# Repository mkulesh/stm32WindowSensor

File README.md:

# stm32WindowSensor

*RF window sensors: STM32L + RFM69 + Android*

This is a DIY windows monitorig system that consist of:
- A window sensor based on STM32L051 MCU and RFM69 RF module. The PCB is developed in EagleCad, firmware written in C++ using System Workbench for STM32
- A server unit also based on STM32L051 MCU and RFM69 RF module
- A server software module (Java) that reads data from server unit and forwards it to the mobile app
- A mobile app for Android written in Java

## Window Sensor

## Server Unit

## Android App

## License

This software is published under the *GNU General Public License, Version 3*

Copyright © 2018-2019 by Mikhail Kulesh

This program is free software: you can redistribute it and/or modify it under the terms of the GNU General Public License as
published by the Free Software Foundation, either version 3 of the License, or (at your option) any later version.

This program is distributed in the hope that it will be useful, but WITHOUT ANY WARRANTY; without even the implied warranty
of MERCHANTABILITY or FITNESS FOR A PARTICULAR PURPOSE.  See the GNU General Public License for more details. You should have
received a copy of the GNU General Public License along with this program.

If not, see [www.gnu.org/licenses](https://www.gnu.org/licenses).

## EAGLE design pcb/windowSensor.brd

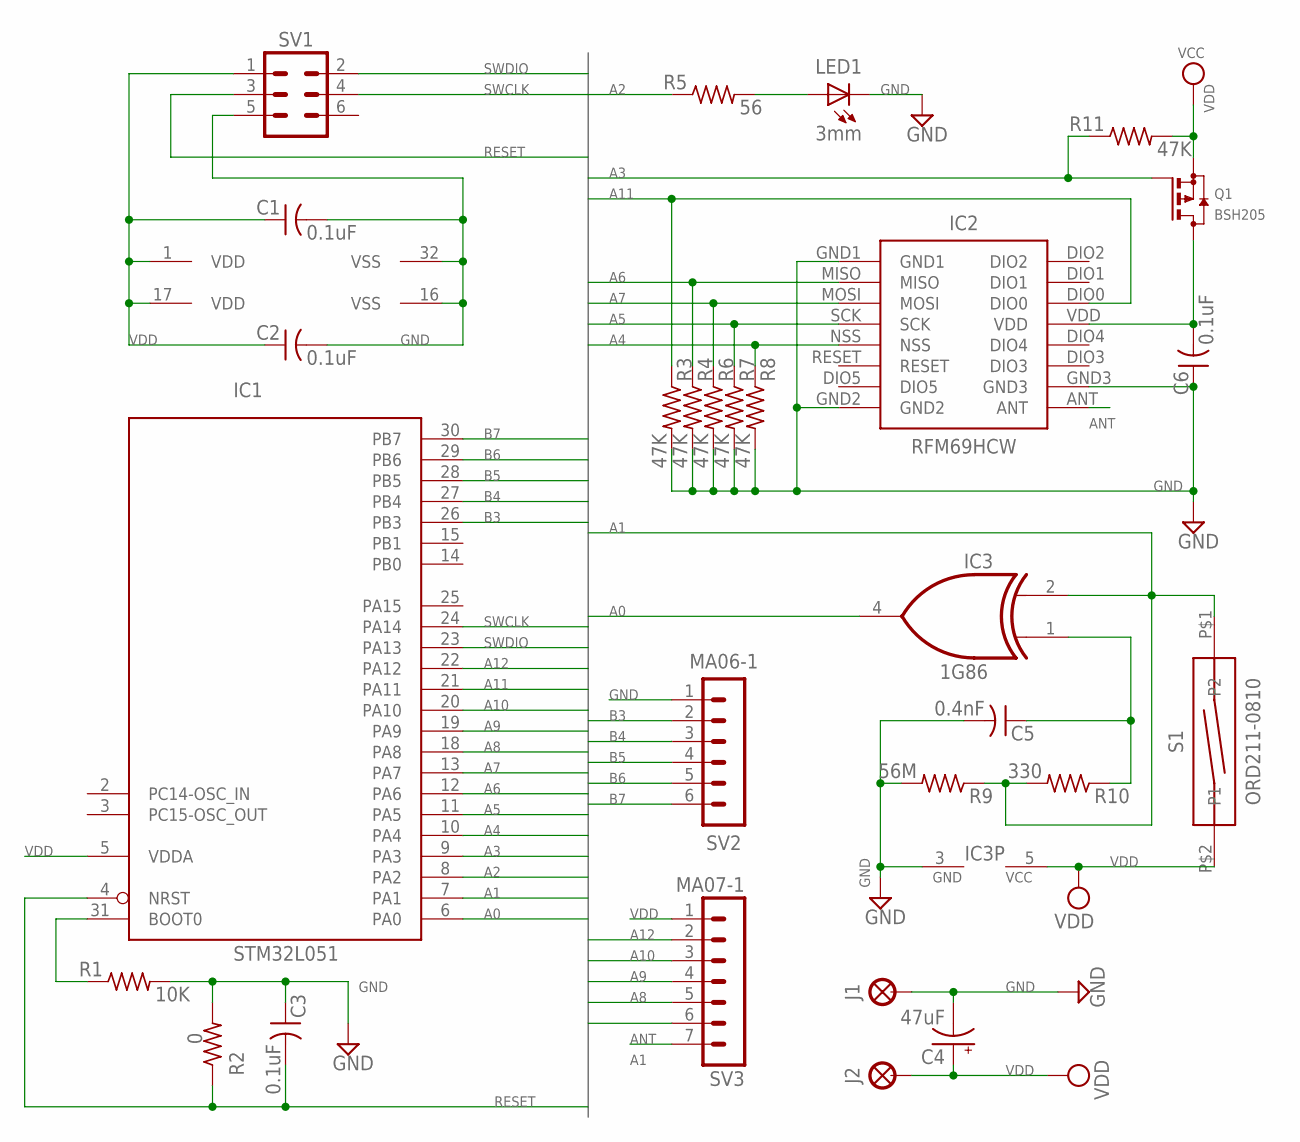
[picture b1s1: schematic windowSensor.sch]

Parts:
C1, C2, C3, C6: 0.1uF; C0805
C4: 47uF; CPOL0805
C5: 0.4nF; C0805
IC1: STM32L051; LQFP32
IC2: RFM69HCW
IC3: 1G86; SC70-5
J1, J2: LSP30-LONG
LED1: 3mm; LED3MM
Q1: BSH205; SOT23
R1: 10K; R0805
R2: 0; R0805
R3, R4, R6, R7, R8, R11: 47K; R0805
R5: 56; R0805
R9: 56M; R0805
R10: 330; R0805
S1: ORD211-0810
SV1: SWD; MA03-2
SV2: MA06-1; MA06-1-NO-PL
SV3: MA07-1; MA07-1-NO-PL

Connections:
A0: IC1.6 (PA0), IC3.4 (O)
A1: IC1.7 (PA1), IC3.2 (I1), R9.1, R10.2, S1.P$1 (P2), SV3.6
A2: IC1.8 (PA2), R5.1
A3: IC1.9 (PA3), Q1.1 (G), R11.1
A4: IC1.10 (PA4), IC2.NSS, R8.1
A5: IC1.11 (PA5), IC2.SCK, R7.1
A6: IC1.12 (PA6), IC2.MISO, R4.1
A7: IC1.13 (PA7), IC2.MOSI, R6.1
A8: IC1.18 (PA8), SV3.5
A9: IC1.19 (PA9), SV3.4
A10: IC1.20 (PA10), SV3.3
A11: IC1.21 (PA11), IC2.DIO0, R3.1
A12: IC1.22 (PA12), SV3.2
A-BOOT: IC1.31 (BOOT0), R1.1
ANT: IC2.ANT, SV3.7
B3: IC1.26 (PB3), SV2.2
B4: IC1.27 (PB4), SV2.3
B5: IC1.28 (PB5), SV2.4
B6: IC1.29 (PB6), SV2.5
B7: IC1.30 (PB7), SV2.6
GND: C1.2, C2.2, C3.1, C4.2- (-), C5.2, C6.1, IC1.16 (VSS), IC1.32 (VSS), IC2.GND1, IC2.GND2, IC2.GND3, IC3.3 (GND), J1.MP, LED1.K (C), R1.2, R2.2, R3.2, R4.2, R6.2, R7.2, R8.2, R9.2, SV1.5, SV2.1
unnamed: LED1.A, R5.2
unnamed: C5.1, IC3.1 (I0), R10.1
RESET: C3.2, IC1.4 (NRST), R2.1, SV1.3
SD-VDD: C6.2, IC2.VDD, Q1.3 (D)
SWCLK: IC1.24 (PA14), SV1.4
SWDIO: IC1.23 (PA13), SV1.2
VDD: C1.1, C2.1, C4.1+ (+), IC1.1 (VDD), IC1.5 (VDDA), IC1.17 (VDD), IC3.5 (VCC), J2.MP, Q1.2 (S), R11.2, S1.P$2 (P1), SV1.1, SV3.1

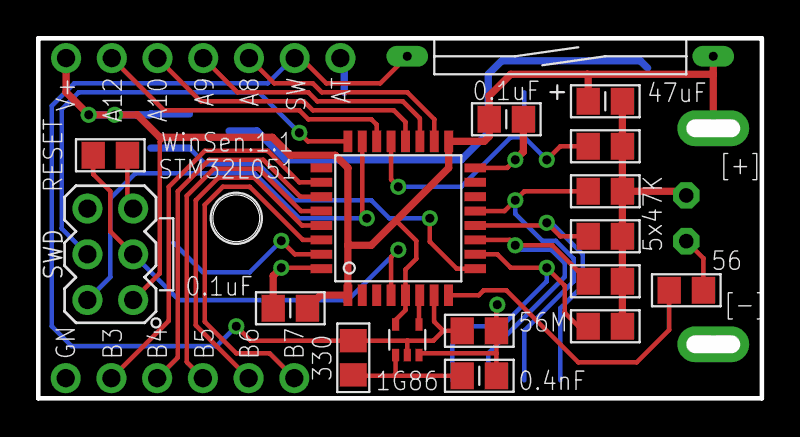
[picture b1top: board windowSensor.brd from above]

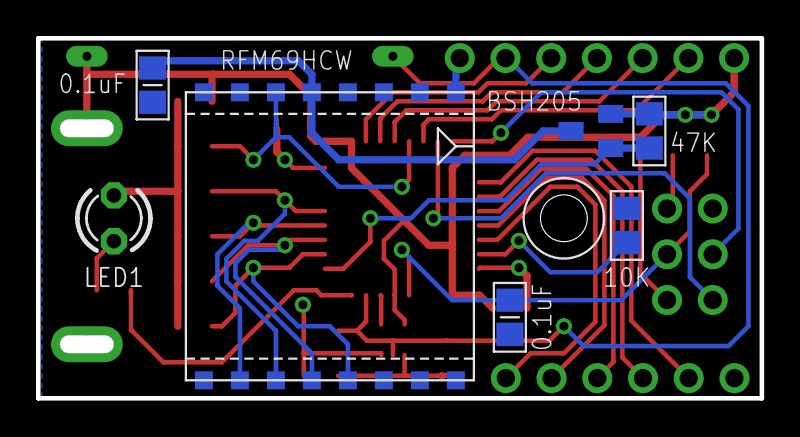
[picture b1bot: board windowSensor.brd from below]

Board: 2 copper layers, 40.2 x 20.0 mm, 28 parts (7 on the bottom side), 28 nets.

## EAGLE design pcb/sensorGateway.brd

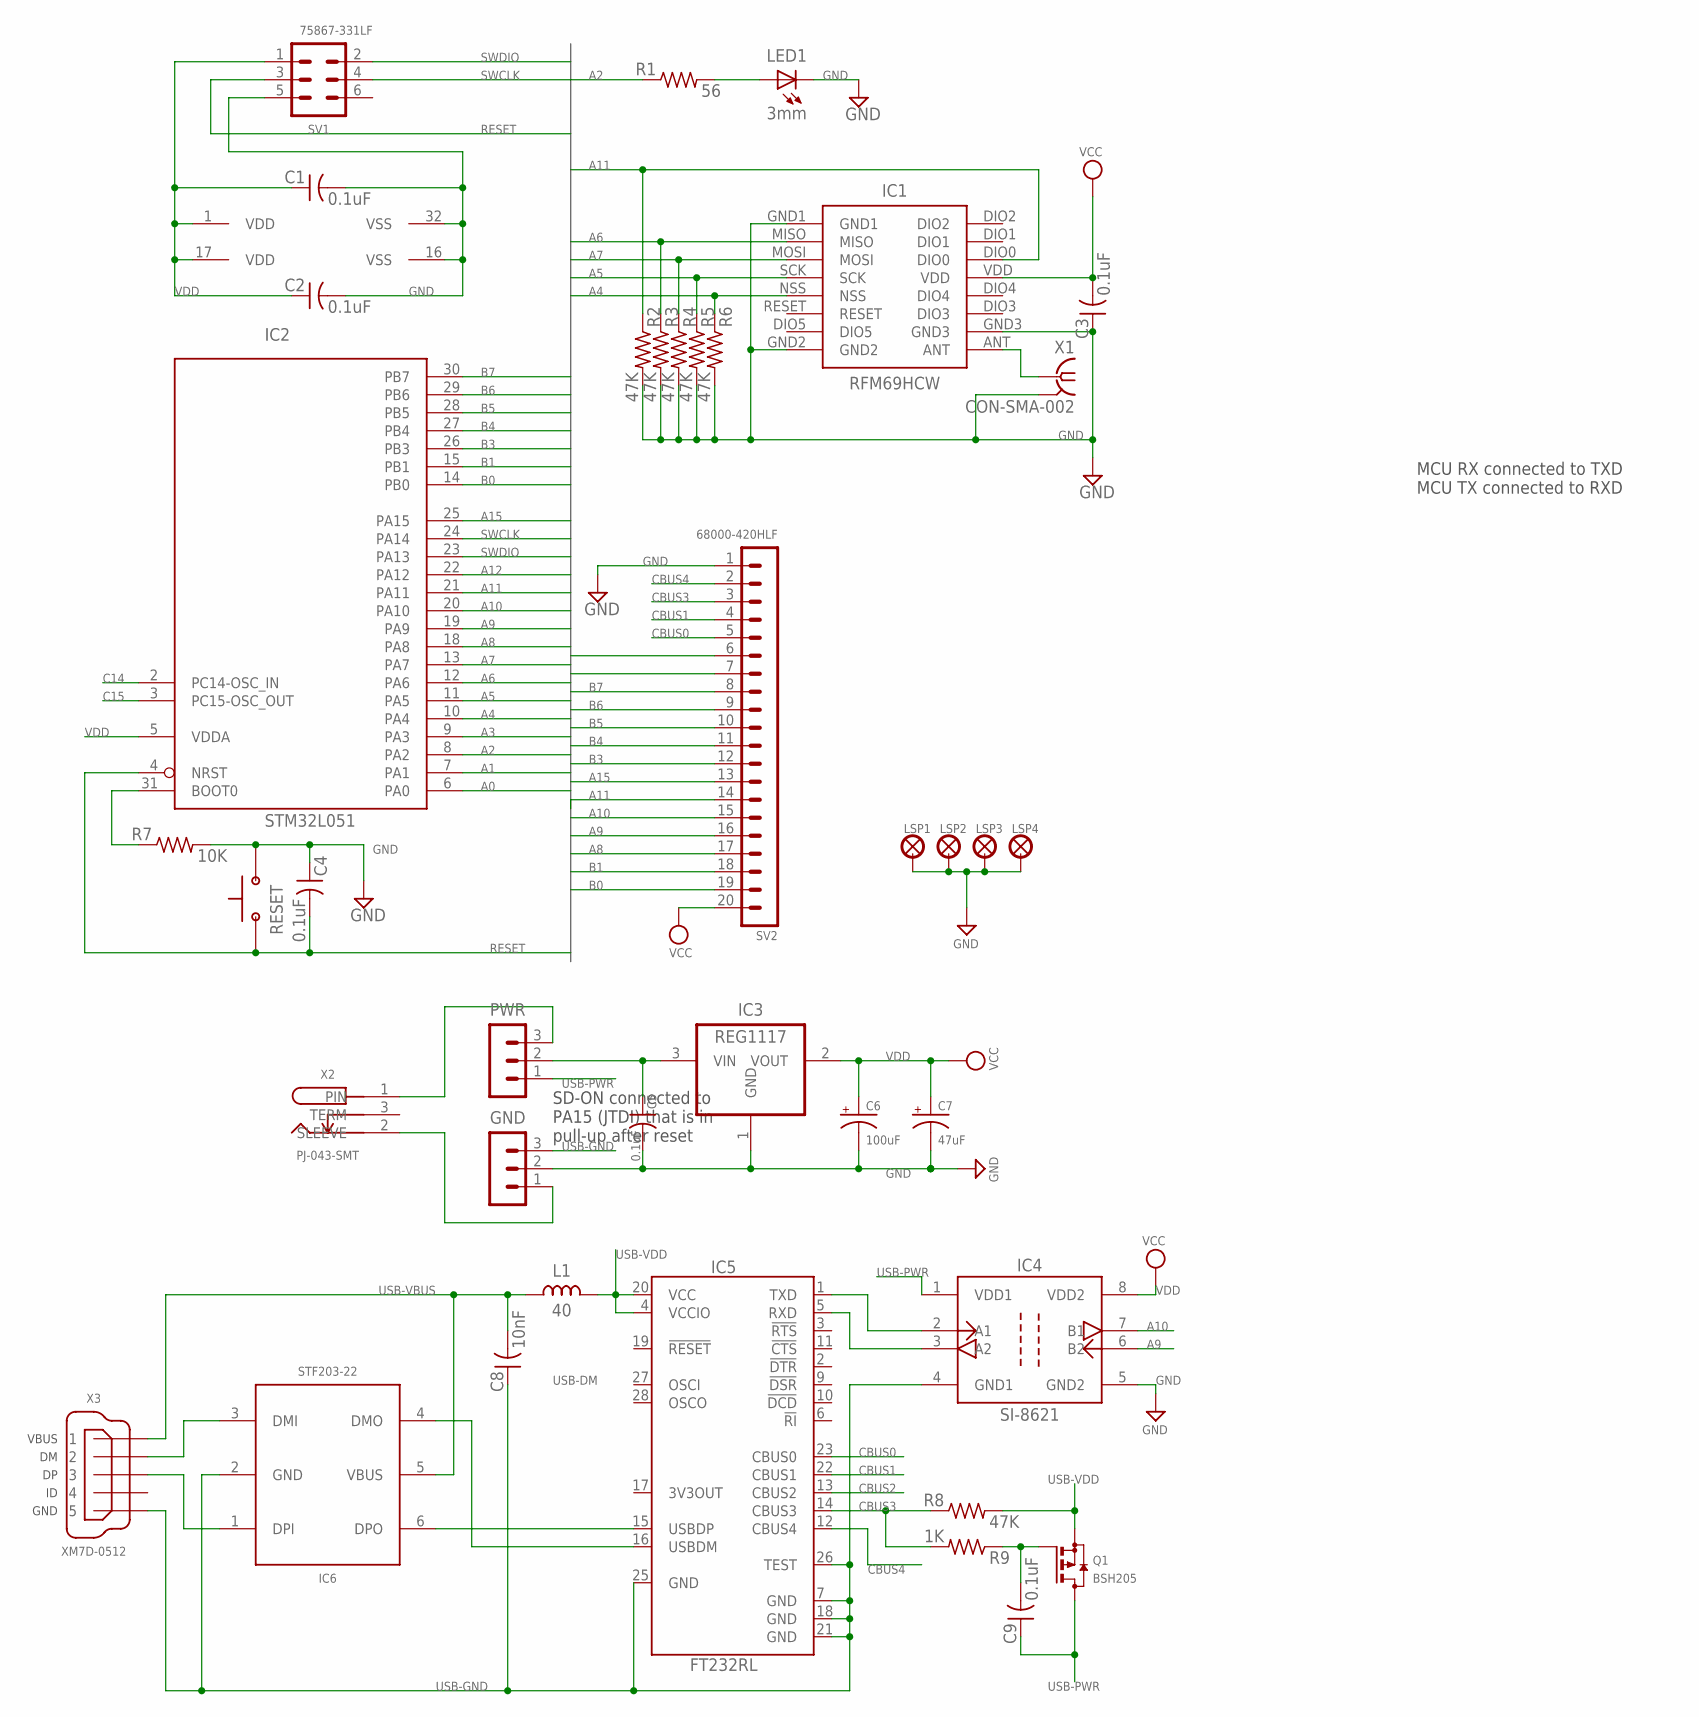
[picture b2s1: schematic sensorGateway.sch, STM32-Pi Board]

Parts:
C1, C2, C3, C4, C5, C9: 0.1uF; C0805
C6: 100uF; CPOL1311
C7: 47uF; CPOL0805
C8: 10nF; C0805
GND: MA03-1PL; MA03-1
IC1: RFM69HCW
IC2: STM32L051; LQFP32
IC3: REG1117; SOT223
IC4: SI-8621; SOIC-8
IC5: FT232RL; SSOP28
IC6: STF203-22; SC70-6
L1: 40; L0805
LED1: 3mm; LED3MM
LSP1, LSP2, LSP3, LSP4: LSP27
PWR: MA03-1PL; MA03-1
Q1: BSH205; SOT23
R1: 56; R0805
R2, R3, R4, R5, R6, R8: 47K; R0805
R7: 10K; R0805
R9: 1K; R0805
RESET: BUTTON-FSM14JRT
SV1: 75867-331LF; MA03-2
SV2: 68000-420HLF; MA20-1-NO-PL
X1: CON-SMA-002; BU-SMA-G
X2: PJ-043-SMT; BUCHSE-1.0X3.2
X3: XM7D-0512

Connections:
A0: IC2.6 (PA0)
A1: IC2.7 (PA1)
A2: IC2.8 (PA2), R1.1
A3: IC2.9 (PA3)
A4: IC1.NSS, IC2.10 (PA4), R6.1
A5: IC1.SCK, IC2.11 (PA5), R5.1
A6: IC1.MISO, IC2.12 (PA6), R3.1
A7: IC1.MOSI, IC2.13 (PA7), R4.1
A8: IC2.18 (PA8), SV2.17
A9: IC2.19 (PA9), IC4.6 (B2), SV2.16
A10: IC2.20 (PA10), IC4.7 (B1), SV2.15
A11: IC1.DIO0, IC2.21 (PA11), R2.1, SV2.14
A12: IC2.22 (PA12)
A15: IC2.25 (PA15), SV2.13
A-BOOT: IC2.31 (BOOT0), R7.1
B0: IC2.14 (PB0), SV2.19
B1: IC2.15 (PB1), SV2.18
B3: IC2.26 (PB3), SV2.12
B4: IC2.27 (PB4), SV2.11
B5: IC2.28 (PB5), SV2.10
B6: IC2.29 (PB6), SV2.9
B7: IC2.30 (PB7), SV2.8
C14: IC2.2 (PC14-OSC_IN), SV2.7
C15: IC2.3 (PC15-OSC_OUT), SV2.6
CBUS0: IC5.23 (CBUS0), SV2.5
CBUS1: IC5.22 (CBUS1), SV2.4
CBUS2: IC5.13 (CBUS2)
CBUS3: IC5.14 (CBUS3), R8.1, R9.2, SV2.3
CBUS4: IC5.12 (CBUS4), SV2.2
GND: C1.2, C2.2, C3.1, C4.1, C5.2, C6.2- (-), C7.2- (-), GND.2, IC1.GND1, IC1.GND2, IC1.GND3, IC2.16 (VSS), IC2.32 (VSS), IC3.1 (GND), IC4.5 (GND2), LED1.K (C), LSP1.MP, LSP2.MP, LSP3.MP, LSP4.MP, R2.2, R3.2, R4.2, R5.2, R6.2, R7.2, RESET.P$2 (2), SV1.5, SV2.1, X1.2, X1.3 (2), X1.4 (2), X1.5 (2)
unnamed: LED1.A, R1.2
unnamed: IC1.ANT, X1.1
unnamed: C9.2, Q1.1 (G), R9.1
unnamed: IC4.2 (A1), IC5.1 (TXD)
unnamed: GND.1, X2.2 (SLEEVE)
unnamed: IC4.3 (A2), IC5.5 (RXD)
unnamed: PWR.3, X2.1 (PIN)
unnamed: IC6.1 (DPI), X3.3
unnamed: IC6.3 (DMI), X3.2
RESET: C4.2, IC2.4 (NRST), RESET.P$1 (1), SV1.3
SWCLK: IC2.24 (PA14), SV1.4
SWDIO: IC2.23 (PA13), SV1.2
USB-DM: IC5.16 (USBDM), IC6.4 (DMO)
USB-DP: IC5.15 (USBDP), IC6.6 (DPO)
USB-GND: C8.1, GND.3, IC4.4 (GND1), IC5.7 (GND), IC5.18 (GND), IC5.21 (GND), IC5.25 (GND), IC5.26 (TEST), IC6.2 (GND), X3.5
USB-PWR: C9.1, IC4.1 (VDD1), PWR.1, Q1.3 (D)
USB-VBUS: C8.2, IC6.5 (VBUS), L1.1, X3.1
USB-VDD: IC5.4 (VCCIO), IC5.20 (VCC), L1.2, Q1.2 (S), R8.2
VDD: C1.1, C2.1, C3.2, C6.1+ (+), C7.1+ (+), IC1.VDD, IC2.1 (VDD), IC2.5 (VDDA), IC2.17 (VDD), IC3.2 (VOUT), IC4.8 (VDD2), SV1.1, SV2.20
VIN: C5.1, IC3.3 (VIN), PWR.2

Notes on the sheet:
SD-ON connected to PA15 (JTDI) that is in pull-up after reset
MCU RX connected to TXD MCU TX connected to RXD

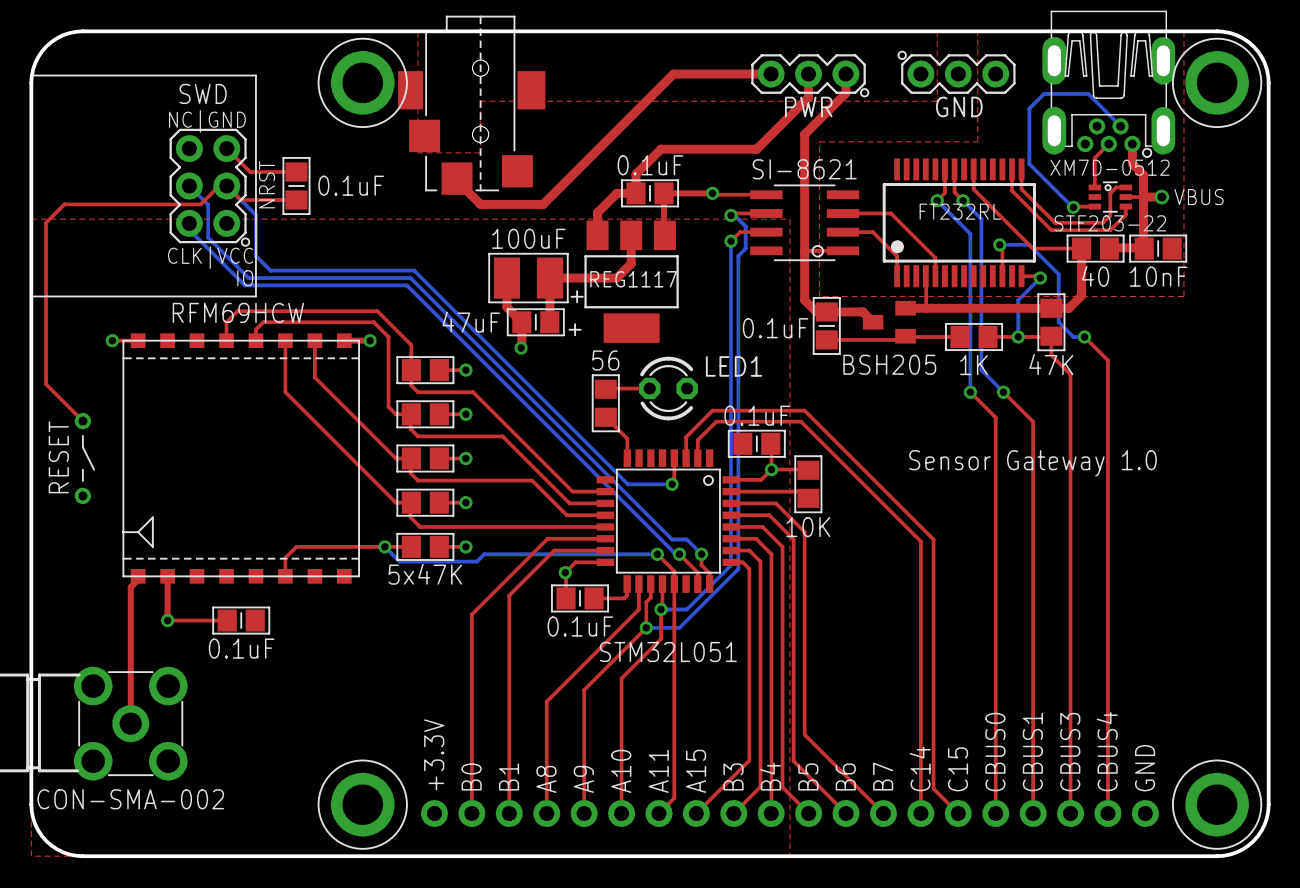
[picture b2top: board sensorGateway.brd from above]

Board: 2 copper layers, 84.0 x 56.0 mm, 39 parts (0 on the bottom side), 45 nets.

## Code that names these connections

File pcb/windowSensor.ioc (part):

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Mcu.Name=STM32L051K(6-8)Tx
Mcu.Package=LQFP32
Mcu.UserName=STM32L051K8Tx
PA0.Mode=Wake_Up_1
PA0.Signal=SYS_WKUP1
PA1.GPIOParameters=GPIO_Label
PA1.GPIO_Label=pinSwithValue
PA1.Signal=GPIO_Input
PA10.Mode=Asynchronous
PA10.Signal=USART1_RX
PA11.GPIOParameters=GPIO_Label
PA11.GPIO_Label=pinDio0
PA11.Signal=GPIO_Input
PA13.Mode=Serial_Wire
PA13.Signal=SYS_SWDIO
PA14.Mode=Serial_Wire
PA14.Signal=SYS_SWCLK
PA2.GPIOParameters=GPIO_Label
PA2.GPIO_Label=pinLed
PA2.Signal=S_TIM2_CH3
PA3.GPIOParameters=GPIO_Label
PA3.GPIO_Label=pinRfmPower
PA3.Signal=GPIO_Output
PA4.Mode=NSS_Signal_Hard_Output
PA4.Signal=SPI1_NSS
PA5.Mode=Full_Duplex_Master
PA5.Signal=SPI1_SCK
PA6.Mode=Full_Duplex_Master
PA6.Signal=SPI1_MISO
PA7.Mode=Full_Duplex_Master
PA7.Signal=SPI1_MOSI
PA9.Mode=Asynchronous
PA9.Signal=USART1_TX
RCC.SYSCLKFreq_VALUE=2097000

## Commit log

2019-12-24 Added release directory
2020-01-06 Updated gitignore
2020-01-31 Updated androidSVG library
2020-01-31 Updated target version
2020-01-31 Updated copyright
2020-01-31 Fixed lint warnings: declaration redundancy
2020-01-31 Fixed compiler warnings in communication task
2020-01-31 Fixed lint warnings: redundant conversion
2020-01-31 Fixed lint warnings: Java 7 issues
2020-01-31 Fixed lint warnings: added SuppressLint
2020-02-01 Fixed lint warnings: sensor info expanded by battery state
2020-02-01 Fixed lint warnings: Added server password
2020-02-06 Released version 1.2
2020-03-10 Updated Gradle version
2021-04-05 moved cubeMX files

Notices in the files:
README.md:
License: GNU GPLv3
